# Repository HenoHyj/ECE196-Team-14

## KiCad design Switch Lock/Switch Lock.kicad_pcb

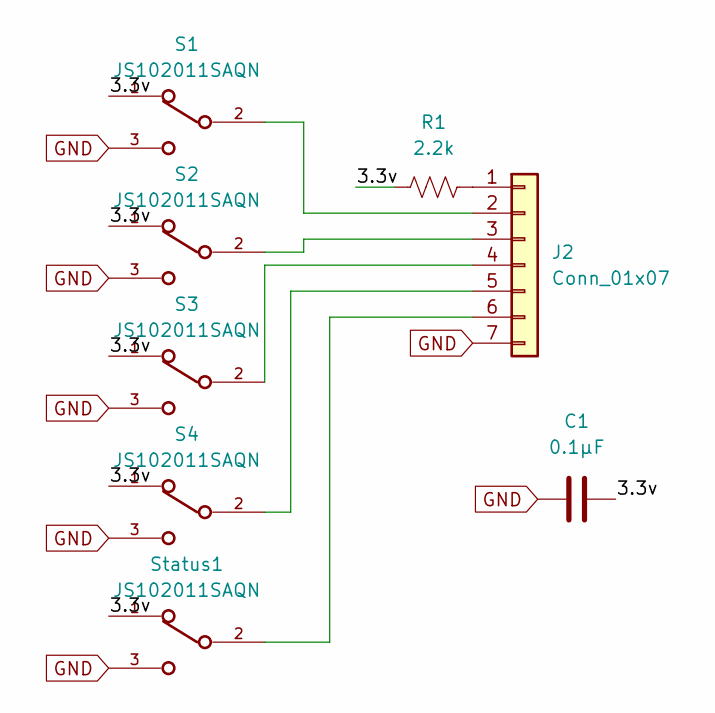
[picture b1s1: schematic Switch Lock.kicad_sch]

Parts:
C1: 0.1μF; C_0805_2012Metric_Pad1.18x1.45mm_HandSolder
J2: Conn_01x07; PinHeader_1x07_P2.54mm_Vertical
R1: 2.2k; R_0805_2012Metric_Pad1.20x1.40mm_HandSolder
S1, S2, S3, S4: JS102011SAQN; SW_JS102011SAQN
Status1: JS102011SAQN; SW_JS102011SAQN

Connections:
/3.3v: C1.2, R1.1, S1.1, S2.1, S3.1, S4.1, Status1.1
GND: C1.1, J2.7, S1.3, S2.3, S3.3, S4.3, Status1.3
unnamed: J2.1, R1.2
unnamed: J2.2, S1.2
unnamed: J2.3, S2.2
unnamed: J2.4, S3.2
unnamed: J2.5, S4.2
unnamed: J2.6, Status1.2

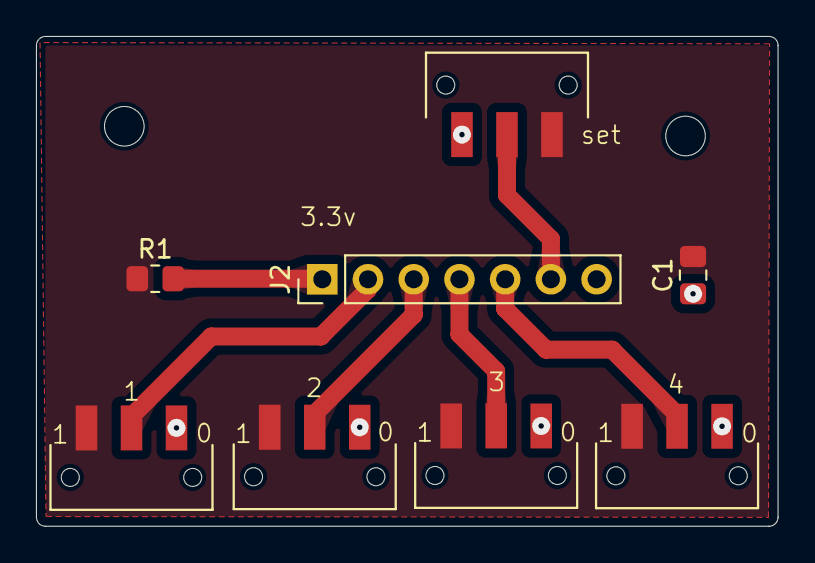
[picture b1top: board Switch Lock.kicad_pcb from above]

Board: 2 copper layers, 41.2 x 27.2 mm, 8 parts (0 on the bottom side), 8 nets.

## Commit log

2024-11-09 Switch Lock Schematic Design Uploaded
2024-11-11 finisheddesign
2024-11-11 gbrsUpdate
2024-11-11 finishedpcbdesign
2024-11-11 update febracation stuff
2024-11-15 3dmodoling
2024-11-19 cratePlatformIOProject
